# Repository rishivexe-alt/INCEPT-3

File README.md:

# INCEPT-3

### Selectable 3.3 V / 5 V / 12 V DC–DC Buck Converter

INCEPT-3 is a 15 V-input, three-mode buck-converter design built around a TLC555-based PWM controller and a discrete high-side P-channel MOSFET power stage. The project brings together analog control circuitry, USB-C Power Delivery input handling, power-stage design, protection logic, circuit simulation, schematic capture and two-layer PCB development.

I developed the circuit architecture and its supporting design assets from the ground up, using KiCad for the electrical schematic and PCB workflow, NI Multisim as part of the circuit-design/simulation workflow, and Python/SPICE tools for modelling, automated analysis and waveform visualisation.

---

## Project at a glance

| Parameter | Design |
|---|---|
| Project name | **INCEPT-3** |
| Converter topology | Asynchronous buck converter |
| Input | 15 V DC, USB-C PD source |
| Selectable outputs | 3.3 V / 5 V / 12 V |
| PWM controller | TLC555 CMOS timer |
| Switching frequency | Approximately 25 kHz |
| Power switch | FDS4435A P-channel MOSFET |
| Gate driver | MMBT2222A NPN transistor |
| Freewheel diode | SS34 Schottky diode |
| Output filter | 1 mH inductor, 220 µF capacitor, 100 nF bypass |
| Design approach | Open-loop, resistor-calibrated PWM selection |
| PCB | Two-layer KiCad design |

The three voltage settings are calibrated operating targets for a 15 V input and a 10 Ω load. The design uses selectable timing-resistor networks to set the PWM behaviour for each output mode.

## Design preview

**PCB layout**

**Electrical schematic**

**Startup response across the three output modes**

**Steady-state switching waveforms**

## Key features

- Three selectable output-voltage modes: 3.3 V, 5 V and 12 V.
- TLC555-based PWM generation with a diode-steered timing network.
- Three-position, non-shorting rotary selection with selector-valid interlocking.
- Discrete NPN gate drive for a P-channel high-side MOSFET.
- Asynchronous buck power stage with Schottky freewheeling path.
- USB-C PD input stage and auxiliary 12 V control rail.
- Soft-start, undervoltage lockout, output-overvoltage detection and overcurrent hiccup control.
- Python-based circuit-generation, calibration and waveform-analysis utilities.
- KiCad schematic, PCB, BOM, netlist, fabrication outputs and design documentation.

## System architecture

```text
USB-C PD 15 V INPUT
        │
        ▼
PD SINK + INPUT PROTECTION
        │
        ▼
15 V INPUT / CURRENT-SENSE NETWORK
        │
        ├──────────────► 12 V AUXILIARY RAIL
        │                         │
        │                         ▼
        │                 TLC555 + LM339 + TL431
        │                         │
        │                 SELECTABLE PWM CONTROL
        │                         │
        ▼                         ▼
P-CHANNEL MOSFET ◄──── NPN GATE DRIVER
        │
        ▼
SWITCHING NODE ──► INDUCTOR ──► OUTPUT FILTER ──► VOUT
        │                                      3.3 V / 5 V / 12 V
        ▼
SCHOTTKY FREEWHEEL DIODE
```

## Hardware design

The hardware is organised into functional blocks: USB-C PD input and protection, auxiliary supply and voltage reference, 555 PWM generation, rotary mode selection, comparator-based supervision, MOSFET gate driving and the buck-converter power stage.

The TLC555 operates from the 12 V auxiliary rail. Its 4.7 nF timing capacitor is charged and discharged through separate diode-steered paths. The selected RA/RB pair determines the timing characteristics for the requested output mode. The timer output drives an MMBT2222A transistor, which controls the gate of the FDS4435A P-channel MOSFET. An SS34 Schottky diode provides the inductor freewheeling path when the MOSFET is off.

The control and protection network includes an L78L12 auxiliary regulator, TL431 reference, LM339 comparator sections, selector-valid interlock, soft-start network, undervoltage detection, output-voltage monitoring and current-sense-based hiccup response.

## Selected component values

| Component | Value / part |
|---|---|
| Input voltage | 15 V DC |
| Timer | TLC555CDR |
| Timing capacitor | 4.7 nF C0G/NP0 |
| Inductor | 1 mH |
| Output capacitor | 220 µF, 25 V |
| Output bypass | 100 nF |
| Main MOSFET | FDS4435A |
| Gate driver | MMBT2222A |
| Freewheel diode | SS34 |
| Current-sense resistor | 0.15 Ω |
| Soft-start capacitor | 2.2 µF |

### Mode selection

| Mode | RA | RB | Target output |
|---|---:|---:|---:|
| 3.3 V | 953 Ω | 9.76 kΩ | 3.3 V |
| 5 V | 2.21 kΩ | 8.66 kΩ | 5 V |
| 12 V | 7.5 kΩ | 3.4 kΩ | 12 V |

## Simulation results

The supplied simulation result set includes startup response, steady-state switching waveforms, load sweeps, input-voltage sweeps, short-circuit response, output-energy injection, selector transitions and input-dropout behaviour.

The reported ngspice results at 15 V input and 10 Ω load are: 

| Metric | 3.3 V mode | 5 V mode | 12 V mode |
|---|---:|---:|---:|
| Average output voltage | 3.303 V | 4.966 V | 11.944 V |
| Output ripple (peak-to-peak) | 5.6 mV | 7.0 mV | 4.2 mV |
| Inductor current range | 0.341–0.448 A | 0.493–0.628 A | 1.218–1.301 A |
| Switching frequency | 25.3 kHz | 25.0 kHz | 25.1 kHz |
| Simulated efficiency | 62.5% | 72.9% | 86.8% |

All values in this table are simulation results from the supplied model and test conditions.

## PCB design

The KiCad PCB is a two-layer board with a 132 mm × 92 mm outline, ground copper pours, ground stitching vias, four M3 mounting holes and nine labelled test points. The layout places the USB-C input on the left and the output connector on the right, with dedicated areas for the control, protection and power-stage circuitry.

The project includes the editable KiCad schematic and PCB, project symbol and footprint libraries, BOM, netlist exports, PCB DRC report, schematic and PCB PDFs, Gerber layers, drill data and component-position output.

## Repository structure

```text
INCEPT-3/
├── README.md
├── docs/
│   ├── TECHNICAL_REPORT.md
│   └── design-history/
├── hardware/
│   └── kicad/
│       ├── buck555.kicad_pro
│       ├── buck555.kicad_sch
│       ├── buck555.kicad_pcb
│       ├── buck555_BOM.csv
│       ├── generators/
│       └── fab/
├── simulation/
│   ├── ngspice/
│   └── spice-reference/
└── results/
    └── plots/
```

## Tools and technologies

- **KiCad 7:** schematic capture, symbols, footprints, PCB layout and manufacturing exports.
- **NI Multisim:** circuit design and simulation workflow.
- **ngspice:** SPICE-based transient simulation and model execution for the included reproducible result set.
- **Python:** design automation, calibration utilities, simulation orchestration and waveform analysis.
- **NumPy / Matplotlib:** numerical processing and engineering plots.
- **Freerouting:** PCB autorouting workflow.

## Opening the design

1. Clone or download this repository.
2. Open `hardware/kicad/buck555.kicad_pro` in KiCad.
3. Open `buck555.kicad_sch` for the complete electrical schematic.
4. Open `buck555.kicad_pcb` to inspect the two-layer board.
5. Refer to `docs/TECHNICAL_REPORT.md` for the circuit architecture, pin connections, calculations and simulation results.

The project was authored with KiCad 7.0.11 file formats.

## Simulation assets

The `simulation/ngspice/` directory contains the netlist generator, device models, operating-mode suites, fault-analysis scripts and text result summaries. The `simulation/spice-reference/` directory contains the mode-specific SPICE references and component-to-node mapping used to reproduce the circuit in a SPICE-oriented simulator.

For the Python/ngspice workflow, install Python 3, NumPy and ngspice, then run the suite scripts from `simulation/ngspice/` so generated RAW and log files remain alongside the simulation sources. The plotting script in `results/plots/` reads those generated RAW files and writes the corresponding plots.

## Project focus

INCEPT-3 explores the integration of analog PWM control, discrete power switching, protection logic, circuit simulation and PCB design in a single selectable-output power-conversion system.

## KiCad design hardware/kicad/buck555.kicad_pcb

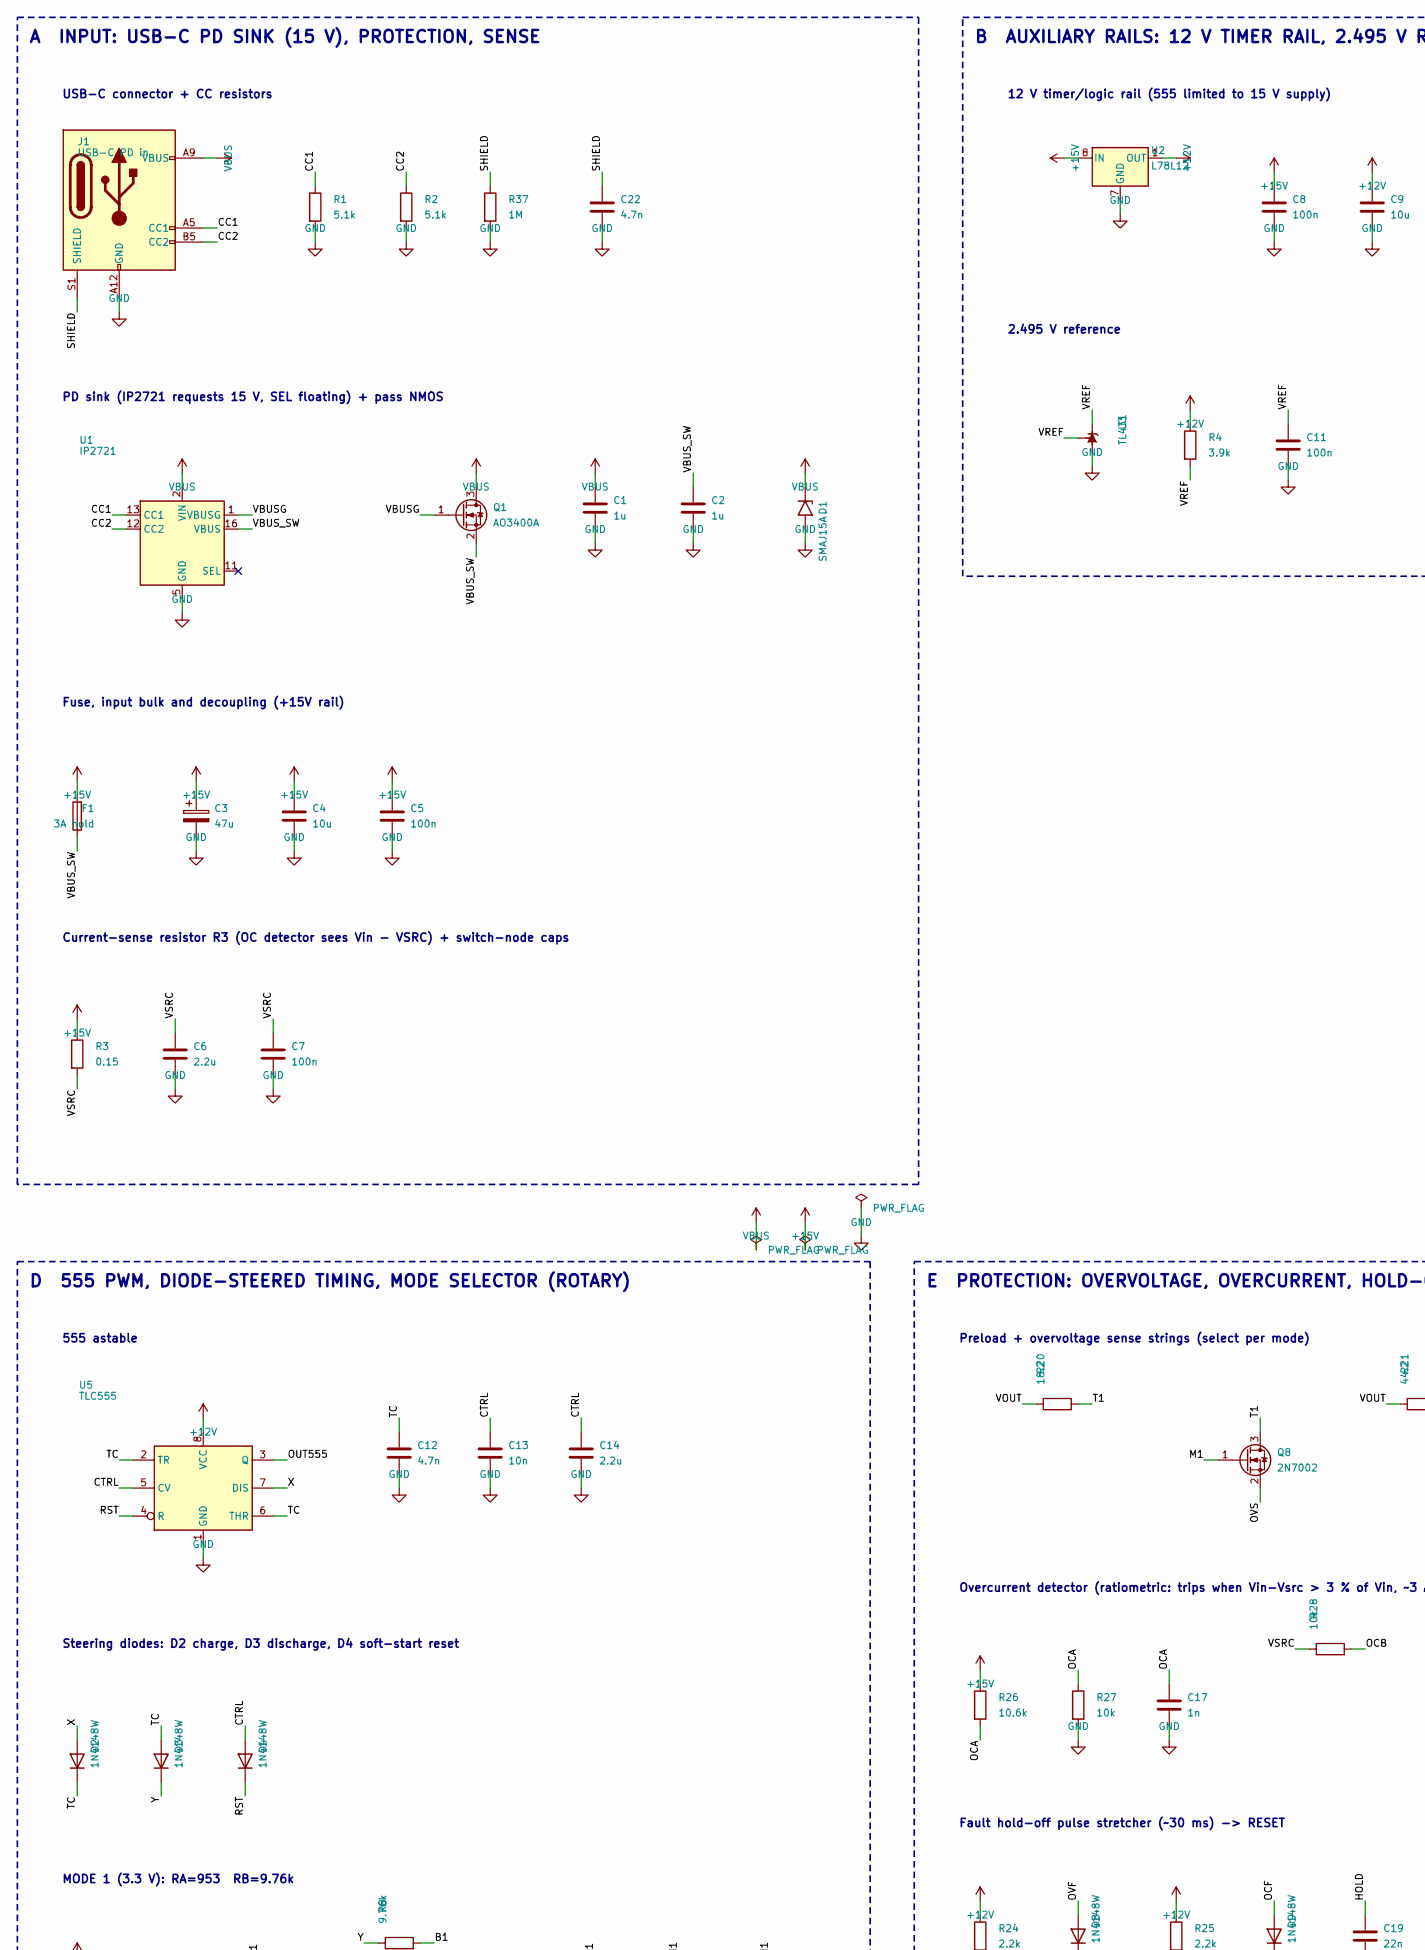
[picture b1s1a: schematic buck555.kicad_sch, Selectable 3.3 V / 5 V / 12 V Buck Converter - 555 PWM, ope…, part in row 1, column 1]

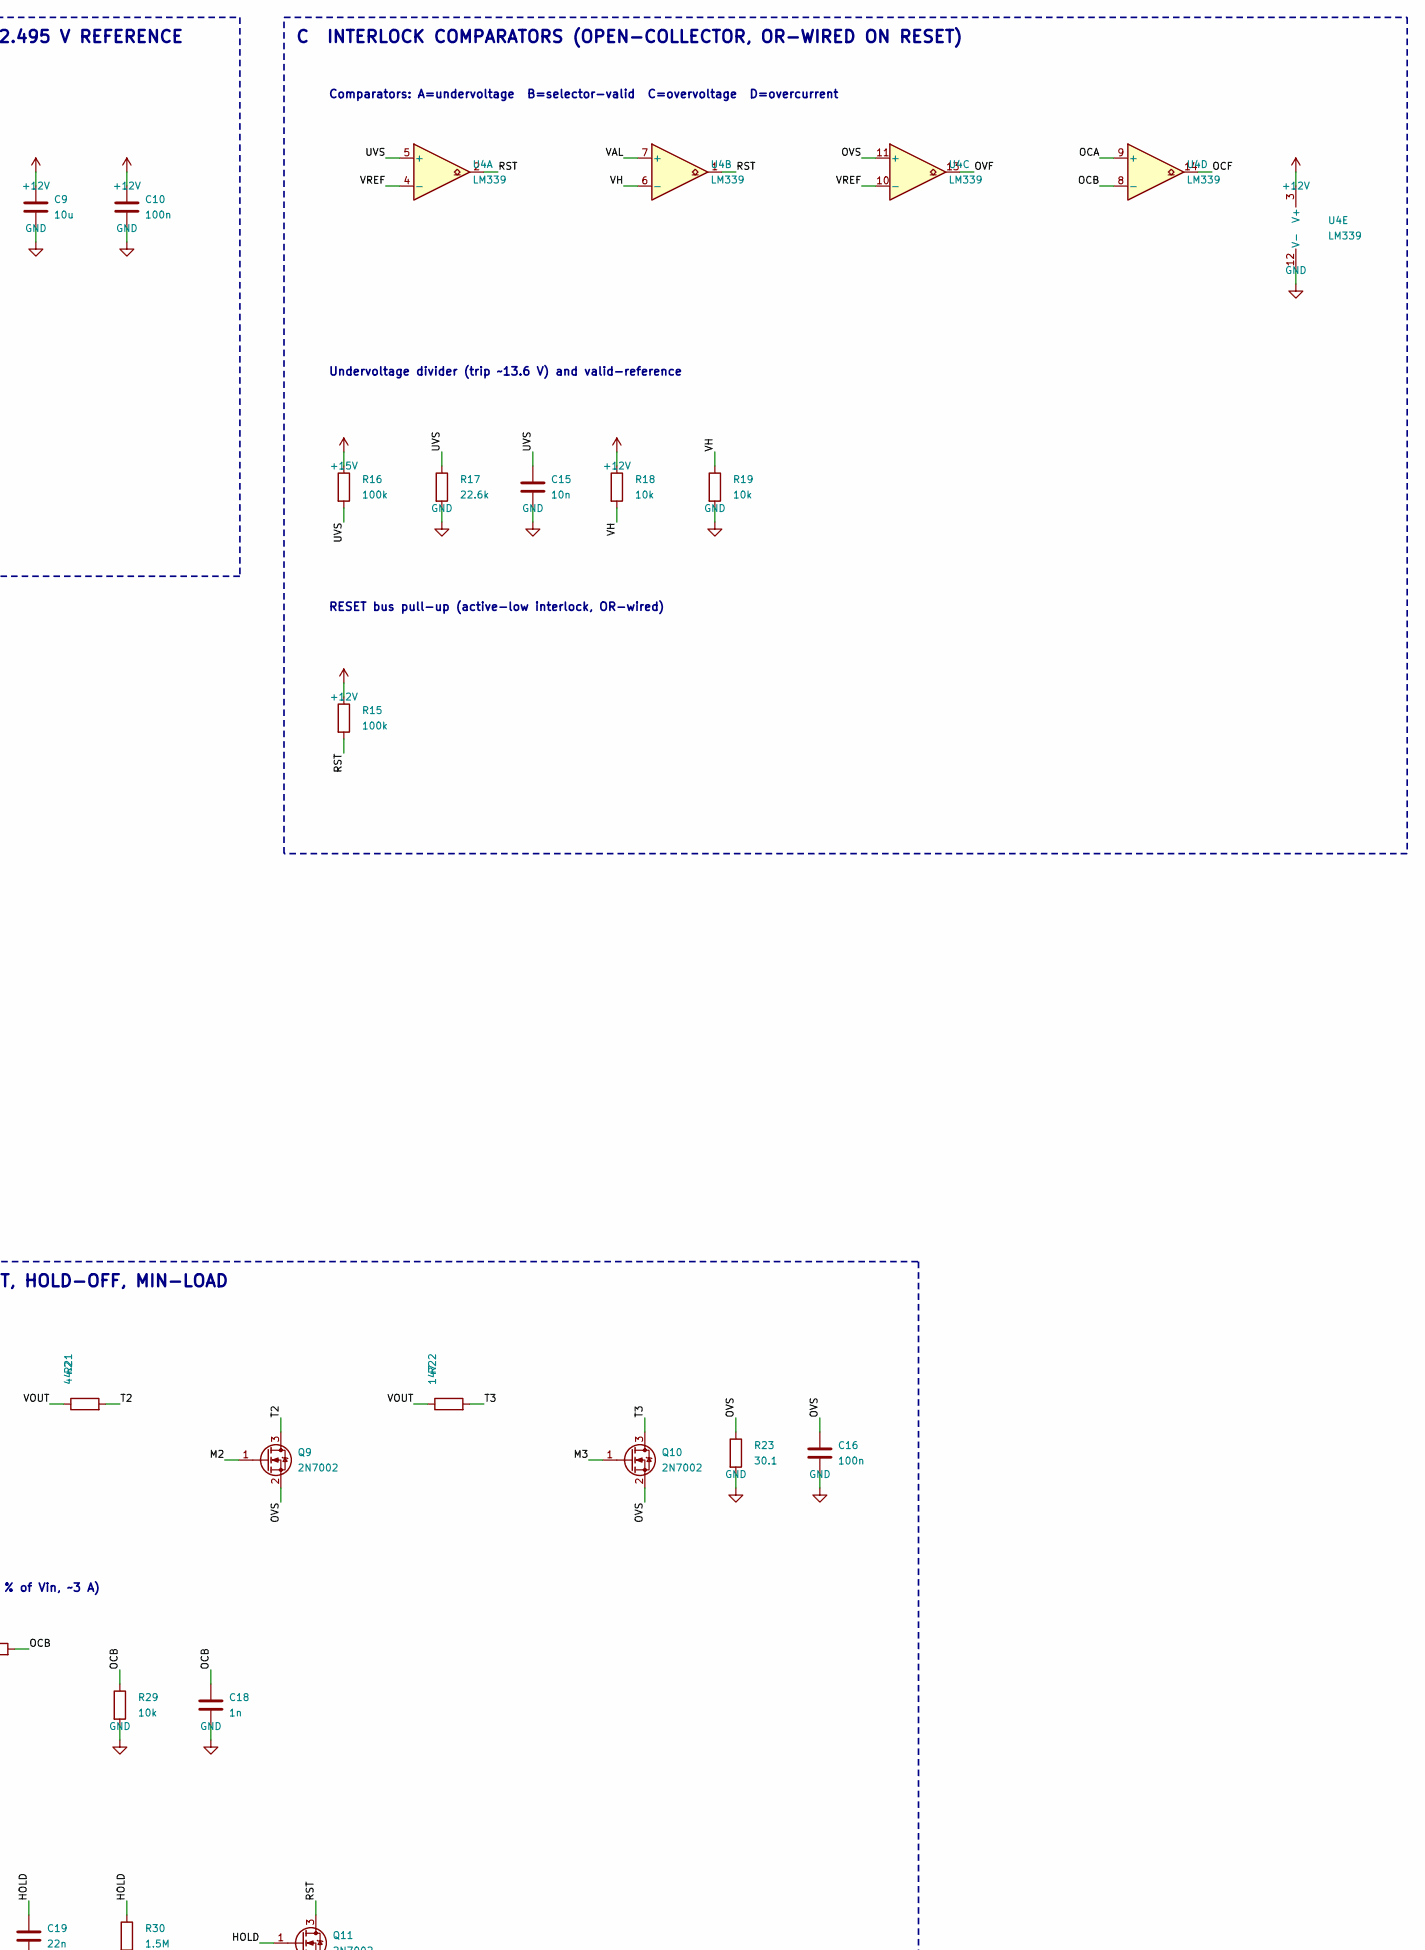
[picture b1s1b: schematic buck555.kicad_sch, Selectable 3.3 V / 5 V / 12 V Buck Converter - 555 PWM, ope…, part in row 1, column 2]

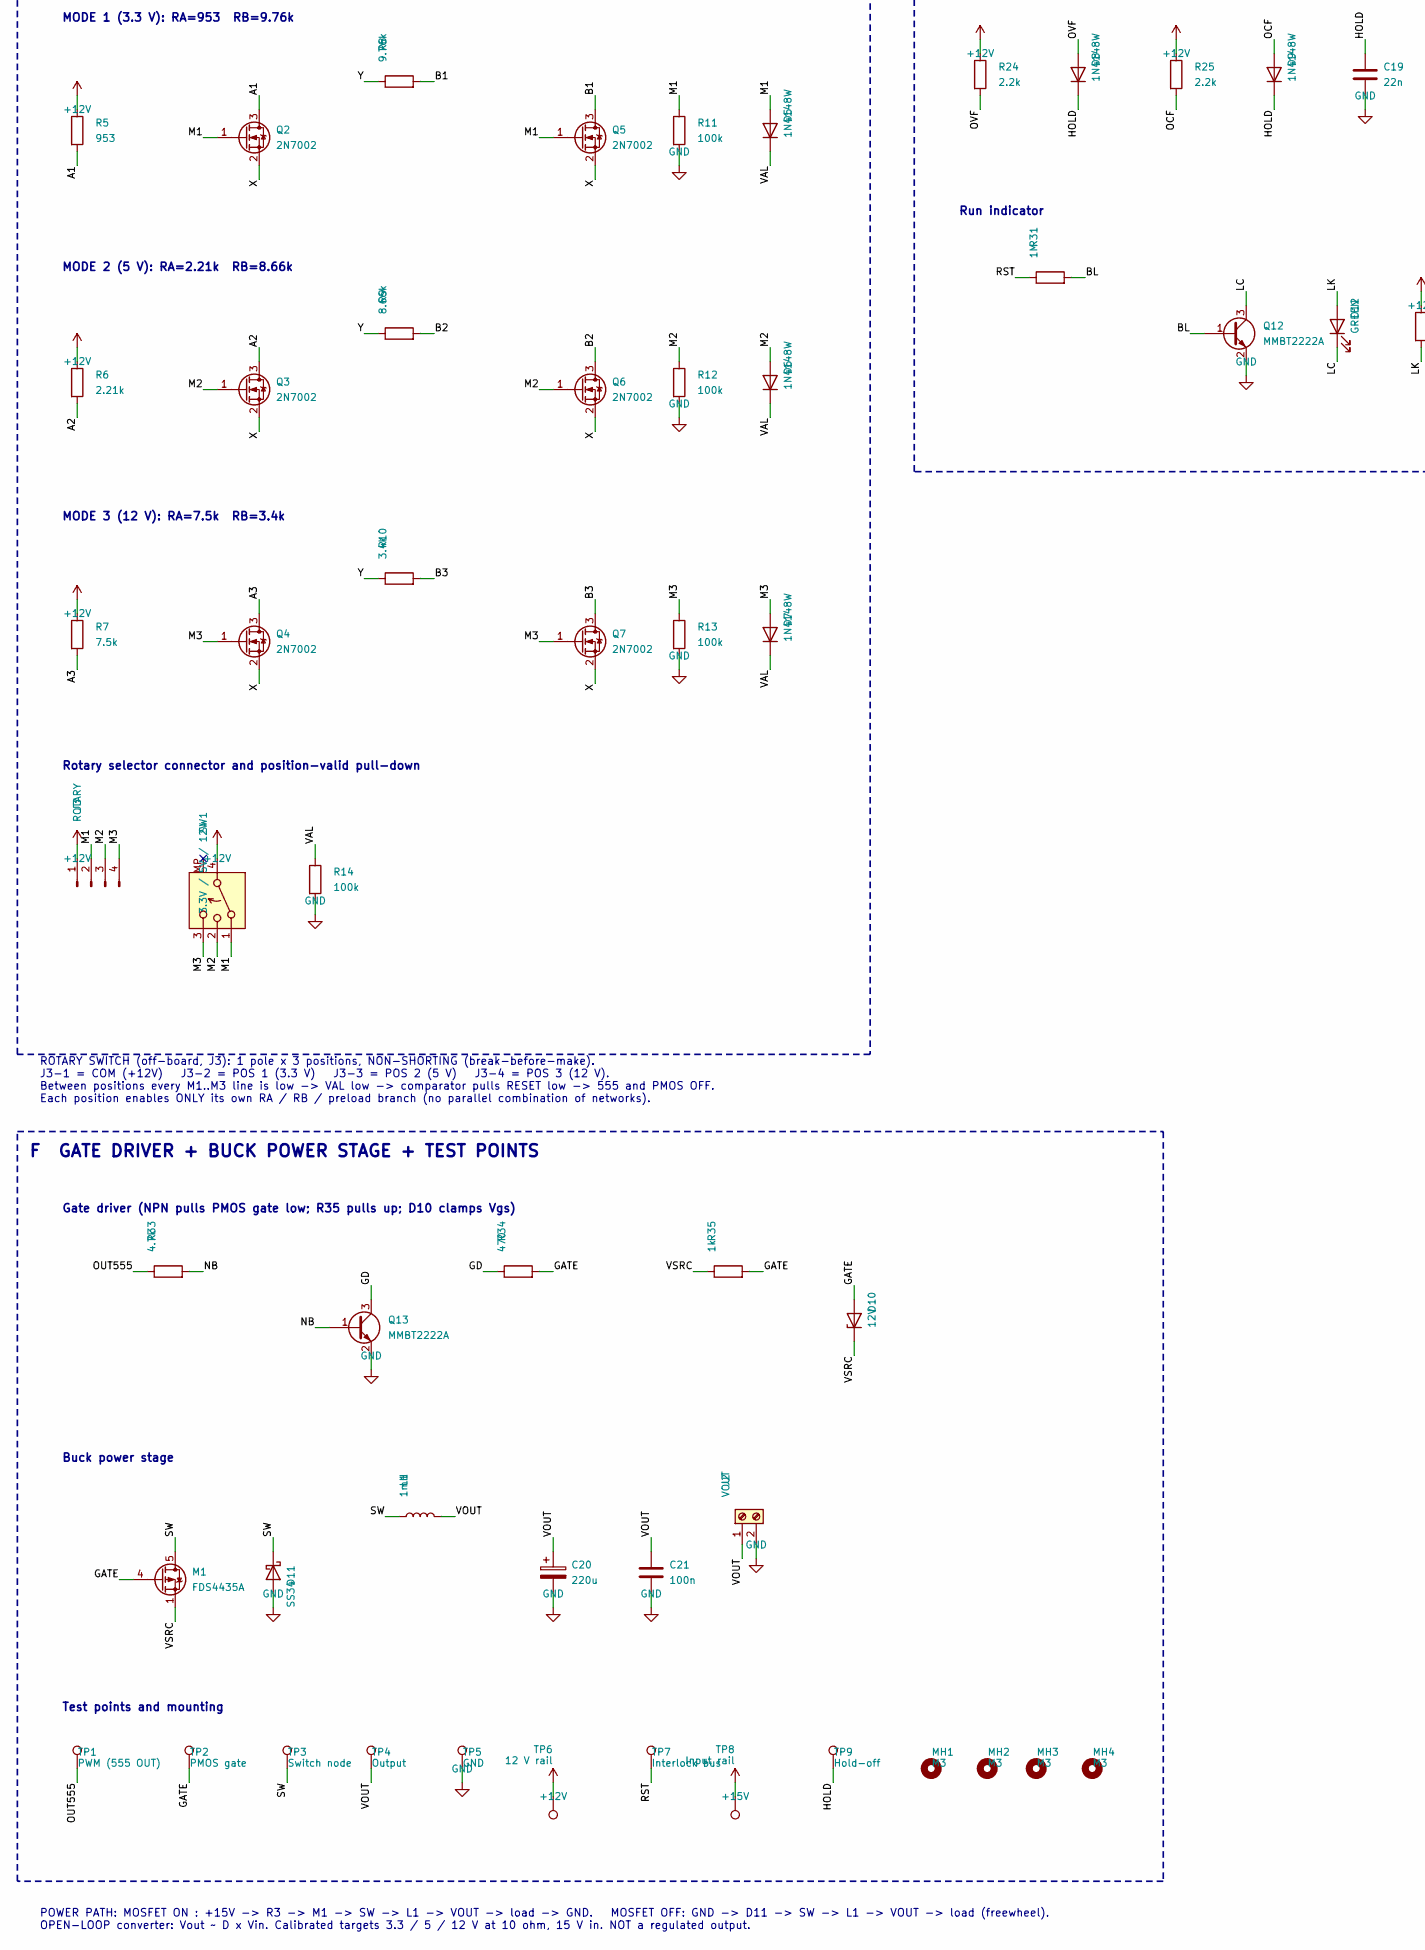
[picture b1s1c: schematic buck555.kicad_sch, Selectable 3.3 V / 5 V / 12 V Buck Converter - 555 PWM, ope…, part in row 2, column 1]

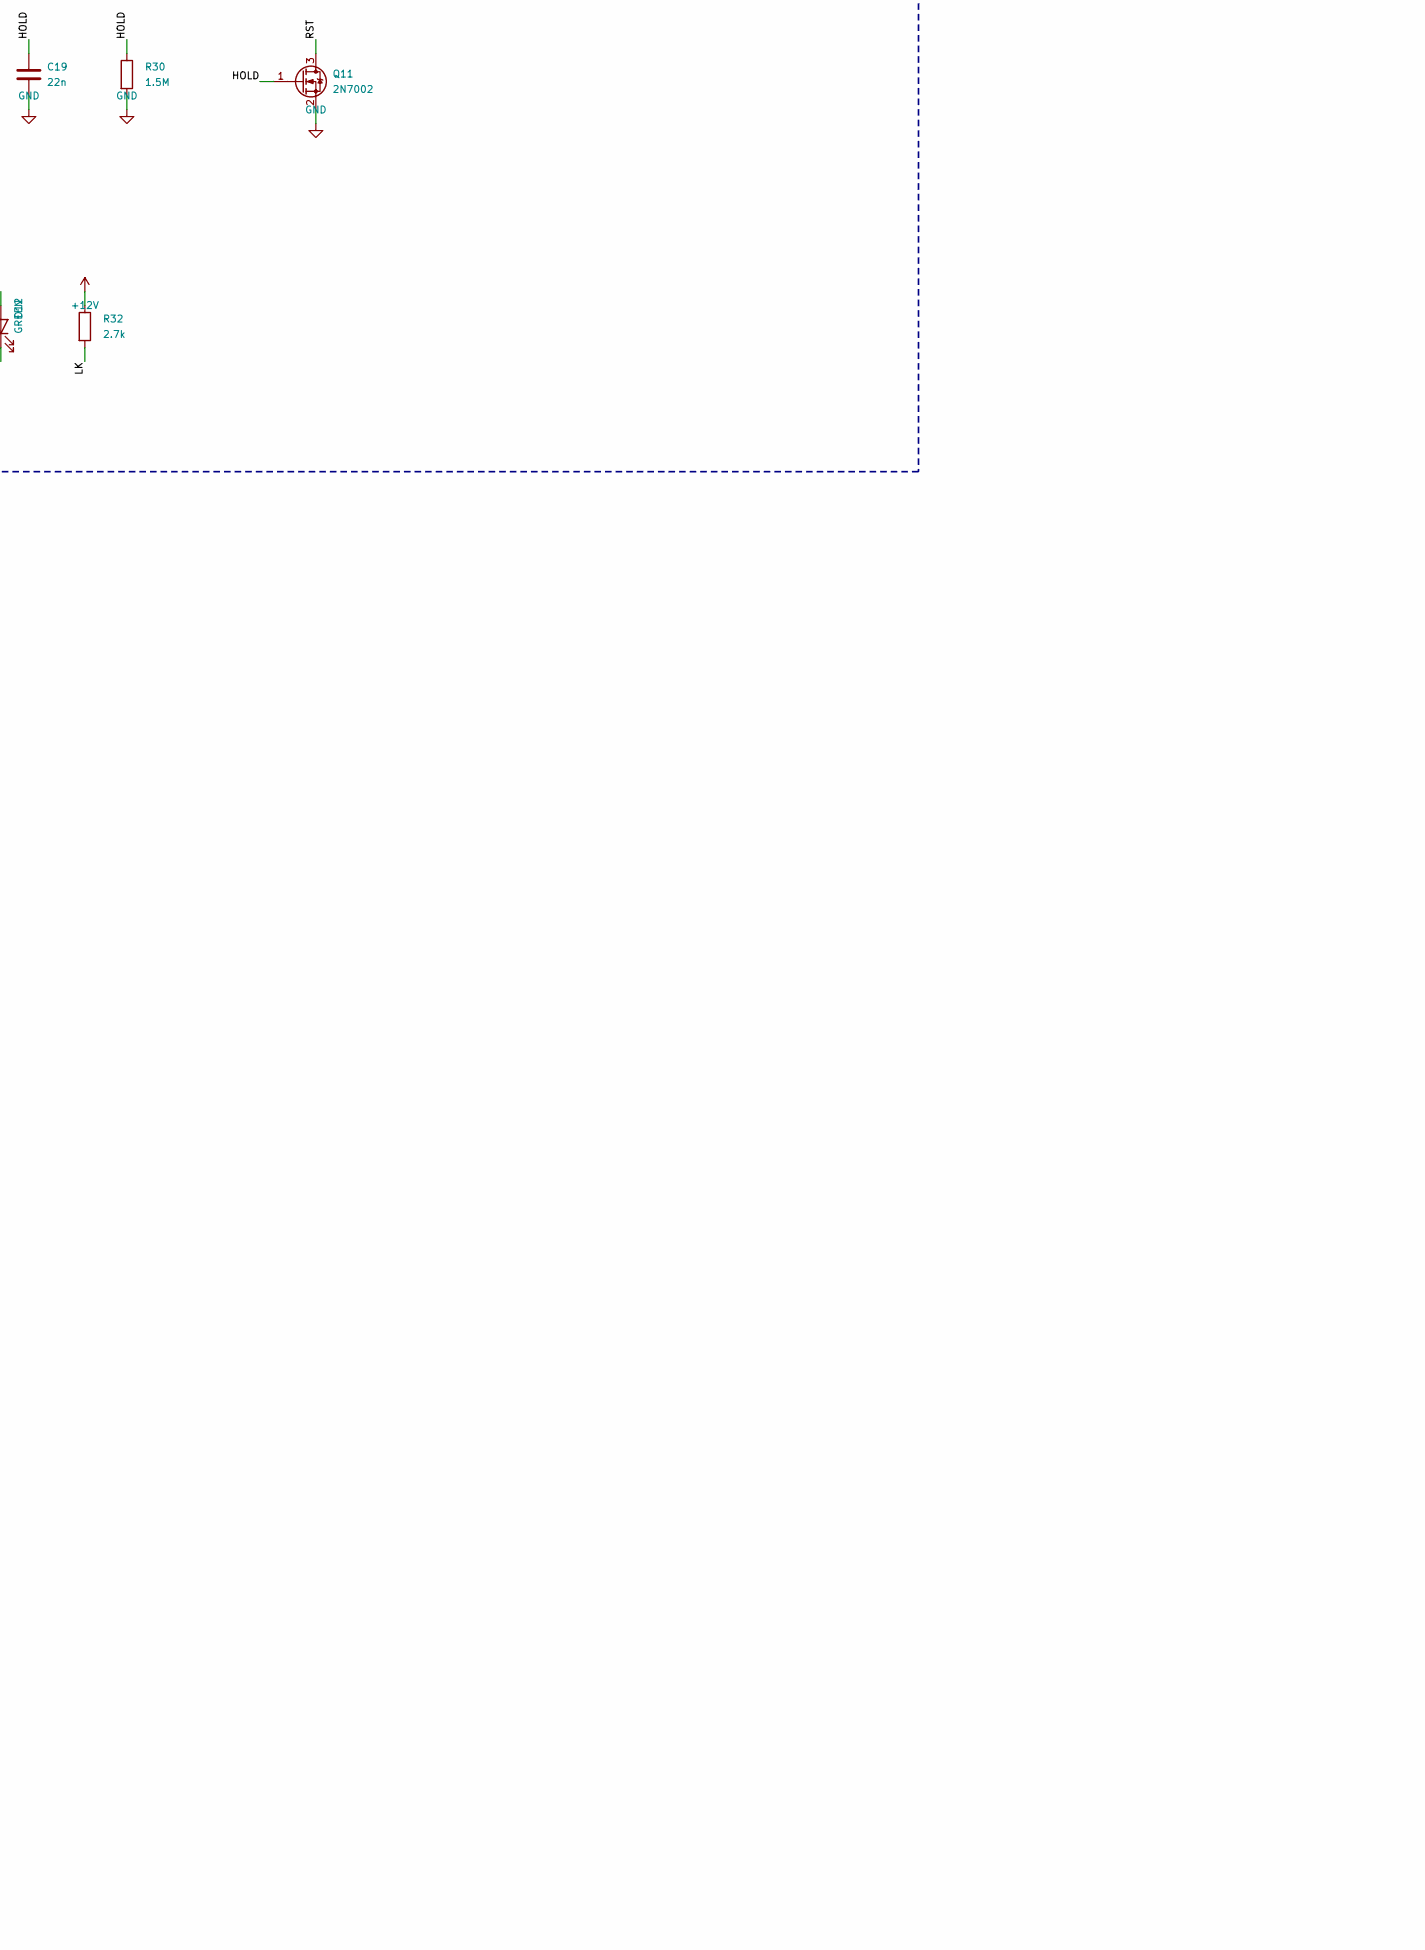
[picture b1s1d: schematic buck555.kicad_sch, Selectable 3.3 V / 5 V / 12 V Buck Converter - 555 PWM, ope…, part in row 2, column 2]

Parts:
C1, C2: 1u; C_0603_1608Metric; MPN GRM188R71H105KA61D
C3: 47u; CP_Elec_6.3x7.7; MPN EEE-FK1E470P
C4: 10u; C_1210_3225Metric; MPN GRM32ER71E106KA12L
C5, C7, C8, C10, C11, C16, C21: 100n; C_0603_1608Metric; MPN CC0603KRX7R9BB104
C6: 2.2u; C_1206_3216Metric; MPN GRM31CR71E225KA73L
C9: 10u; C_1206_3216Metric; MPN GRM31CR71E106KA12L
C12: 4.7n; C_0603_1608Metric; MPN GCM1885C1H472JA16D
C13, C15: 10n; C_0603_1608Metric; MPN CC0603KRX7R9BB103
C14: 2.2u; C_0805_2012Metric; MPN GRM21BR71A225KA01L
C17, C18: 1n; C_0603_1608Metric; MPN CC0603KRX7R9BB102
C19: 22n; C_0603_1608Metric; MPN CC0603KRX7R9BB223
C20: 220u; CP_Elec_8x10; MPN EEE-FK1E221P
C22: 4.7n; C_0603_1608Metric; MPN CC0603KRX7R9BB472
D1: SMAJ15A; D_SMA; MPN SMAJ15A
D2, D3, D4, D5, D6, D7, D8, D9: 1N4148W; D_SOD-123; MPN 1N4148W-7-F
D10: 12V; D_SOD-123; MPN MMSZ5242B-7-F
D11: SS34; D_SMA; MPN SS34-E3/57T
D12: GREEN; LED_0603_1608Metric; MPN 150060GS75000
F1: 3A hold; Fuse_1812_4532Metric; MPN MF-MSMF300/16X-2
J1: USB-C PD in; USB_C_Receptacle_GCT_USB4125-xx-x_6P_TopMnt_Horizontal; MPN USB4125-GF-A
J2: VOUT; TerminalBlock_Phoenix_MKDS-1,5-2-5.08_1x02_P5.08mm_Horizont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; MPN 1729128
J3: ROTARY; PinHeader_1x04_P2.54mm_Vertical; MPN 2.54mm 1x4 header
L1: 1mH; L_Radial_D21.0mm_P19.00mm
M1: FDS4435A; SOIC-8_3.9x4.9mm_P1.27mm; MPN FDS4435A
MH1, MH2, MH3, MH4: M3; MountingHole_3.2mm_M3_Pad_Via
Q1: AO3400A; SOT-23; MPN AO3400A
Q2, Q3, Q4, Q5, Q6, Q7, Q8, Q9, Q10, Q11: 2N7002; SOT-23; MPN 2N7002
Q12, Q13: MMBT2222A; SOT-23; MPN MMBT2222ALT1G
R1, R2: 5.1k; R_0603_1608Metric; MPN RC0603FR-075K1L
R3: 0.15; R_2512_6332Metric; MPN CRM2512-FX-R150ELF
R4: 3.9k; R_0603_1608Metric; MPN RC0603FR-073K9L
R5: 953; R_0603_1608Metric; MPN RC0603FR-07953RL
R6: 2.21k; R_0603_1608Metric; MPN RC0603FR-072K21L
R7: 7.5k; R_0603_1608Metric; MPN RC0603FR-077K5L
R8: 9.76k; R_0603_1608Metric; MPN RC0603FR-079K76L
R9: 8.66k; R_0603_1608Metric; MPN RC0603FR-078K66L
R10: 3.4k; R_0603_1608Metric; MPN RC0603FR-073K4L
R11, R12, R13, R14, R15: 100k; R_0603_1608Metric; MPN RC0603FR-07100KL
R16: 100k; R_0603_1608Metric; MPN RT0603BRD07100KL
R17: 22.6k; R_0603_1608Metric; MPN RT0603BRD0722K6L
R18, R19: 10k; R_0603_1608Metric; MPN RC0603FR-0710KL
R20: 18.2; R_2512_6332Metric; MPN RC2512FR-0718R2L
R21: 44.2; R_2512_6332Metric; MPN RC2512FR-0744R2L
R22: 147; R_2512_6332Metric; MPN RC2512FR-07147RL
R23: 30.1; R_2512_6332Metric; MPN RC2512FK-0730R1L
R24, R25: 2.2k; R_0603_1608Metric; MPN RC0603FR-072K2L
R26: 10.6k; R_0603_1608Metric; MPN RT0603BRD0710K6L
R27, R28, R29: 10k; R_0603_1608Metric; MPN RT0603BRD0710KL
R30: 1.5M; R_0603_1608Metric; MPN RC0603FR-071M5L
R31, R37: 1M; R_0603_1608Metric; MPN RC0603FR-071ML
R32: 2.7k; R_0603_1608Metric; MPN RC0603FR-072K7L
R33: 4.7k; R_0603_1608Metric; MPN RC0603FR-074K7L
R34: 470; R_0603_1608Metric; MPN RC0603FR-07470RL
R35: 1k; R_0603_1608Metric; MPN RC0603FR-071KL
SW1: 3.3V / 5V / 12V
TP1: PWM (555 OUT); TestPoint_Pad_D2.0mm
TP2: PMOS gate; TestPoint_Pad_D2.0mm
TP3: Switch node; TestPoint_Pad_D2.0mm
TP4: Output; TestPoint_Pad_D2.0mm
TP5: GND; TestPoint_Pad_D2.0mm
TP6: 12 V rail; TestPoint_Pad_D2.0mm
TP7: Interlock bus; TestPoint_Pad_D2.0mm
TP8: Input rail; TestPoint_Pad_D2.0mm
TP9: Hold-off; TestPoint_Pad_D2.0mm
U1: IP2721; TSSOP-16_4.4x5mm_P0.65mm; MPN IP2721
U2: L78L12; SOIC-8_3.9x4.9mm_P1.27mm; MPN L78L12ACD13TR
U3: TL431; SOIC-8_3.9x4.9mm_P1.27mm; MPN TL431AIDR
U4: LM339; SOIC-14_3.9x8.7mm_P1.27mm; MPN LM339DR
U5: TLC555; SOIC-8_3.9x4.9mm_P1.27mm; MPN TLC555CDR

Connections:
+12V: C9.1, C10.1, J3.1, R4.1, R5.1, R6.1, R7.1, R15.1, R18.1, R24.1, R25.1, R32.1, SW1.4, TP6.1, U2.1 (OUT), U4.3 (V+), U5.8 (VCC)
+15V: C3.1, C4.1, C5.1, C8.1, F1.2, R3.1, R16.1, R26.1, TP8.1, U2.8 (IN)
A1: Q2.3 (D), R5.2
A2: Q3.3 (D), R6.2
A3: Q4.3 (D), R7.2
B1: Q5.3 (D), R8.2
B2: Q6.3 (D), R9.2
B3: Q7.3 (D), R10.2
BL: Q12.1 (B), R31.2
CC1: J1.A5 (CC1), R1.1, U1.13 (CC1)
CC2: J1.B5 (CC2), R2.1, U1.12 (CC2)
CTRL: C13.1, C14.1, D4.2 (A), U5.5 (CV)
GATE: D10.2 (A), M1.4 (G), R34.2, R35.2, TP2.1
GD: Q13.3 (C), R34.1
GND: C1.2, C2.2, C3.2, C4.2, C5.2, C6.2, C7.2, C8.2, C9.2, C10.2, C11.2, C12.2, C13.2, C14.2, C15.2, C16.2, C17.2, C18.2, C19.2, C20.2, C21.2, C22.2, D1.2 (A2), D11.2 (A), J1.A12 (GND), J1.B12 (GND), J2.2, Q11.2 (S), Q12.2 (E), Q13.2 (E), R1.2, R2.2, R11.2, R12.2, R13.2, R14.2, R17.2, R19.2, R23.2, R27.2, R29.2, R30.2, R37.2, TP5.1, U1.5 (GND), U2.2 (GND), U2.3 (GND), U2.6 (GND), U2.7 (GND), U3.2 (A), U3.3 (A), U3.6 (A), U3.7 (A), U4.12 (V-), U5.1 (GND)
HOLD: C19.1, D8.1 (K), D9.1 (K), Q11.1 (G), R30.1, TP9.1
LC: D12.1 (K), Q12.3 (C)
LK: D12.2 (A), R32.2
M1: D5.2 (A), J3.2, Q2.1 (G), Q5.1 (G), Q8.1 (G), R11.1, SW1.1
M2: D6.2 (A), J3.3, Q3.1 (G), Q6.1 (G), Q9.1 (G), R12.1, SW1.2
M3: D7.2 (A), J3.4, Q4.1 (G), Q7.1 (G), Q10.1 (G), R13.1, SW1.3
NB: Q13.1 (B), R33.2
OCA: C17.1, R26.2, R27.1, U4.9 (+)
OCB: C18.1, R28.2, R29.1, U4.8 (-)
OCF: D9.2 (A), R25.2, U4.14
OUT555: R33.1, TP1.1, U5.3 (Q)
OVF: D8.2 (A), R24.2, U4.13
OVS: C16.1, Q8.2 (S), Q9.2 (S), Q10.2 (S), R23.1, U4.11 (+)
RST: D4.1 (K), Q11.3 (D), R15.2, R31.1, TP7.1, U4.1, U4.2, U5.4 (R)
SHIELD: C22.1, J1.S1 (SHIELD), R37.1
SW: D11.1 (K), L1.1, M1.5 (D), M1.6 (D), M1.7 (D), M1.8 (D), TP3.1
T1: Q8.3 (D), R20.2
T2: Q9.3 (D), R21.2
T3: Q10.3 (D), R22.2
TC: C12.1, D2.1 (K), D3.2 (A), U5.2 (TR), U5.6 (THR)
UVS: C15.1, R16.2, R17.1, U4.5 (+)
VAL: D5.1 (K), D6.1 (K), D7.1 (K), R14.1, U4.7 (+)
VBUS: C1.1, D1.1 (A1), J1.A9 (VBUS), J1.B9 (VBUS), Q1.3 (D), U1.2 (VIN)
VBUSG: Q1.1 (G), U1.1 (VBUSG)
VBUS_SW: C2.1, F1.1, Q1.2 (S), U1.16 (VBUS)
VH: R18.2, R19.1, U4.6 (-)
VOUT: C20.1, C21.1, J2.1, L1.2, R20.1, R21.1, R22.1, TP4.1
VREF: C11.1, R4.2, U3.1 (K), U3.8 (REF), U4.4 (-), U4.10 (-)
VSRC: C6.1, C7.1, D10.1 (K), M1.1 (S), M1.2 (S), M1.3 (S), R3.2, R28.1, R35.1
X: D2.2 (A), Q2.2 (S), Q3.2 (S), Q4.2 (S), Q5.2 (S), Q6.2 (S), Q7.2 (S), U5.7 (DIS)
Y: D3.1 (K), R8.1, R9.1, R10.1

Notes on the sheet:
USB-C connector + CC resistors
PD sink (IP2721 requests 15 V, SEL floating) + pass NMOS
Fuse, input bulk and decoupling (+15V rail)
Current-sense resistor R3 (OC detector sees Vin - VSRC) + switch-node caps
12 V timer/logic rail (555 limited to 15 V supply)
2.495 V reference
Comparators: A=undervoltage B=selector-valid C=overvoltage D=overcurrent
Undervoltage divider (trip ~13.6 V) and valid-reference
RESET bus pull-up (active-low interlock, OR-wired)
555 astable
Steering diodes: D2 charge, D3 discharge, D4 soft-start reset
MODE 1 (3.3 V): RA=953 RB=9.76k
MODE 2 (5 V): RA=2.21k RB=8.66k
MODE 3 (12 V): RA=7.5k RB=3.4k
Rotary selector connector and position-valid pull-down
Preload + overvoltage sense strings (select per mode)
Overcurrent detector (ratiometric: trips when Vin-Vsrc > 3 % of Vin, ~3 A)
Fault hold-off pulse stretcher (~30 ms) -> RESET
Run indicator
Gate driver (NPN pulls PMOS gate low; R35 pulls up; D10 clamps Vgs)
Buck power stage
Test points and mounting
A INPUT: USB-C PD SINK (15 V), PROTECTION, SENSE
B AUXILIARY RAILS: 12 V TIMER RAIL, 2.495 V REFERENCE
C INTERLOCK COMPARATORS (OPEN-COLLECTOR, OR-WIRED ON RESET)
D 555 PWM, DIODE-STEERED TIMING, MODE SELECTOR (ROTARY)
E PROTECTION: OVERVOLTAGE, OVERCURRENT, HOLD-OFF, MIN-LOAD
F GATE DRIVER + BUCK POWER STAGE + TEST POINTS
ROTARY SWITCH (off-board, J3): 1 pole x 3 positions, NON-SHORTING (break-before-make). J3-1 = COM (+12V) J3-2 = POS 1 (3.3 V) J3-3 = POS 2 (5 V) J3-4 = POS 3 (12 V). Between positions every M1..M3 line is low -> VAL low -> comparator pulls RESET low -> 555 and PMOS OFF. Each position enables ONLY i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
POWER PATH: MOSFET ON : +15V -> R3 -> M1 -> SW -> L1 -> VOUT -> load -> GND. MOSFET OFF: GND -> D11 -> SW -> L1 -> VOUT -> load (freewheel). OPEN-LOOP converter: Vout ~ D x Vin. Calibrated targets 3.3 / 5 / 12 V at 10 ohm, 15 V in. NOT a regulated output.
